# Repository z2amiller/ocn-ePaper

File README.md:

# ocn-ePaper

A battery-powered elapsed-time counter with a 2.13-inch e-paper display and a magnetic off switch.
While a magnet sits at the marked end, the board is switched off. Take the magnet away and it powers
up and counts elapsed time in hours and minutes, up to 99:59 (about 100 hours). Put the magnet back
and it powers down several seconds later, leaving the last count on the display; the next time the
magnet comes off, counting starts again from 00:00.

It is the e-paper version of [ocn-LCD](https://github.com/z2amiller/ocn-LCD), which uses a segment
LCD.

The renders leave out the e-paper panel (it lies over the front), its socket, the reed switch and the
CR123A holder (on the back), which have no 3D models. They show a header in J1, which stays empty on
a finished board.

Status: revision 0.1, not yet built. Firmware will be added to this repository. The folded tail's pin
order has not yet been checked against a real panel.

## How it works

- **Counting.** An MSP430FR2111 keeps time from a 32.768 kHz crystal. It spends almost all its time
  in its deepest sleep mode with only the clock running, and wakes to update the display.
- **Display.** The panel is a Good Display GDEY0213B74: 2.13 inches, 250 × 122 pixels, black and
  white. E-paper holds its image with no power at all, so the panel sleeps between updates, and the
  last count stays on the screen after the board powers down. Updating it takes higher positive and
  negative voltages. The panel's own controller makes them with a small boost converter on the board
  (L1, Q2, D1–D3), which runs only during an update.
- **Mounting.** The panel lies display-up over the front of the board, 3 mm above it, with its tail
  folded under it into a socket (DS2) on the board. Every part on the front fits under it; the
  tallest, L1, is 2.6 mm.
- **Power.** A CR123A lithium cell (3 V, about 1,500 mAh) in a holder on the back.
- **Magnet switch.** The magnet closes a normally open reed switch (SW1). That pulls the gate of a
  P-channel MOSFET (Q1) up to the cell voltage and cuts power to everything after it. With the
  magnet away, a 10 MΩ resistor pulls the gate low and the board runs. While switched off, the only
  drain on the cell is that resistor, about 0.3 µA.
- **Reset on purpose, not by accident.** About 20 µF of capacitance after the switch keeps the board
  running for several seconds after the magnet arrives (roughly 5–15 s, depending on the panel's
  sleep current), so a brief knock or switch bounce does not reset the count. Leaving the magnet in
  place longer than that powers the board down. If the magnet arrives during a display update, which
  draws about 3.5 mA, the board stops within milliseconds and the image may be left half-updated
  until the next power-up.

## Power budget

Estimates at 3.0 V and 25 °C, from the TI datasheet (SLASE78) and Good Display's spec for the panel.
They will be replaced by measurements once the firmware is in.

| Item | Counting (magnet away) | Off (magnet in place) | Basis |
|---|---|---|---|
| MCU asleep (LPM3.5), with the 32 kHz crystal and RTC running | 0.44 µA | 0 | Datasheet 0.66 µA typical with the supervisor (SVS) on; turning it off saves about 0.22 µA |
| Panel controller in deep sleep between updates | 1 µA (5 µA max) | 0 | Good Display spec |
| Display updates, once a minute | ~50 µA | 0 | 3.5 mA while updating, 0.42 s for a partial update and 3 s for a full one, with a full refresh after every five partial ones as Good Display recommends |
| MCU awake for each update (writing the image, waiting on BUSY) | ~0.2 µA | 0 | ~10 ms at ~1 mA per update, then light sleep while the panel updates |
| Gate pull-down R3 (10 MΩ across the cell while the reed is closed) | 0 | 0.3 µA | 3.0 V / 10 MΩ |
| Q1 MOSFET leakage while off | – | a few nA | Typical; the datasheet maximum is specified at 30 V |
| Hold-up capacitors, leakage | ~1 nA | 0 | MLCC insulation resistance |
| Reset pull-up, reed switch, unused pins (driven low) | 0 | 0 | No DC path |
| **Total** | **about 52 µA** | **about 0.3 µA** | |

The display updates dominate. One partial update uses as much charge as about 17 minutes of sleep,
and a full refresh as about 2 hours, so the update rate sets the battery life.

Estimated runtime on one CR123A (1,500 mAh nominal), allowing about 1 %/year for the cell's own
self-discharge:

| Mode | Average draw | Estimated runtime |
|---|---|---|
| Counting, display updated once a minute | about 52 µA | about 3 years |
| Counting, display updated every 10 minutes | about 6–10 µA | over 10 years |
| Off (magnet in place) | about 0.3 µA | decades |

The last two are longer than a CR123A's rated shelf life of about 10 years, so in practice the cell's
age sets the limit, not this circuit. Cold reduces the cell's usable capacity, and the panel is
specified to update only between 0 and 50 °C.

Firmware choices that keep it there:
- Update the count once a minute at most; slower updates last much longer.
- Use partial updates, with a full refresh after every five to keep ghosting down.
- Put the panel in deep sleep after each update, and sleep in LPM3 while BUSY is high. Check BUSY
  again after its falling edge wakes the MCU, before sending the next command.
- Leave the voltage supervisor (SVS) off in LPM3.5; it costs about 0.2 µA. The brownout reset stays
  on regardless.
- Keep the panel's RES line driven while the panel is in use, and drive every unused pin low.

## Placing the magnet

The reed switch is at the end marked MAGNET DISABLE and runs along the length of the board. It
responds to field along its own length, so use a magnet magnetized through its flat faces (a
neodymium cylinder or disc), at that end, with its axis along the board and its face toward the
board's end. SW1's axis is 3.2 mm from the board's centreline, so a magnet centred on the board's end
lines up with it closely. A model of a typical 10 × 8 mm N42 cylinder (no nearby steel) gives several
times the switch's ~2–3 mT pull-in out to about 20 mm, even 9 mm off the switch's axis.

**Steel nearby.** The CR123A's case is steel, and it sits on the back directly behind the switch.
That changes the field around the switch, and its effect hasn't been measured yet. Check the
switching distance on the bench with a cell fitted.

The switch lets go only once the magnet is a few centimeters away (the same model puts it at about
35–40 mm in line), so move the magnet well clear to start counting.

## Key parts

| Ref | Part | LCSC |
|---|---|---|
| U1 | TI MSP430FR2111IPW, TSSOP-16 | C2052845 |
| DS2 | Good Display GDEY0213B74 2.13" e-paper panel, in a Hirose FH34SRJ-24S-0.5SH socket | C324726 (the socket) |
| BT1 | MYOUNG BH-123A-A1CJ002 CR123A holder, through-hole | C5290177 |
| SW1 | Littelfuse 59170-1-S-00-D reed switch, normally open, 10–15 AT | C315909 |
| Q1 | AO3401A P-channel MOSFET, SOT-23 (power switch) | C15127 |
| Q2 | Vishay Si1308EDL N-channel MOSFET, SOT-323 (display booster) | C469327 |
| L1 | Changjiang FNR4030S470MT 47 µH inductor, 4 × 4 mm | C167888 |
| D1–D3 | 1N5819WS Schottky diode, SOD-323 | C191023 |
| Y1 | 32.768 kHz crystal, 3215, 12.5 pF | C32346 |

Every part in the BOM carries its LCSC number. The panel itself comes from Good Display; DS2's BOM
line is its socket. J1 and TP3 are left out of the BOM and the placement file, and so are BT1 and
SW1, which are fitted by hand. The passives are 0603 and 1206.

## Assembly

1. **Surface-mount parts, all on the front.** A stencil helps with the 0.65 mm pitch MCU. The reed
   switch is rated for reflow and can go on with the rest.
2. **CR123A holder on the back, by hand.** Trim its two pins close on the front afterwards. Untrimmed,
   they stand about 2.5 mm proud, under a panel that sits 3 mm up.
3. **Program the MCU** (see below). J1 ends up under the panel, so do this before the panel goes on.
4. **Panel.** Open the socket's latch and slide the tail in, with the panel lying face down beyond the
   end of the board nearest the socket, then close the latch. Fold the panel over onto a 3 mm spacer on the front, so it lies
   display-up over the board. Double-sided foam tape works as the spacer and keeps pressure off the
   glass.
5. **Battery.** Fit the CR123A last, matching the + and − marks on the back.

## Programming

The MCU is programmed over Spy-Bi-Wire from the eZ-FET programmer on a TI MSP-EXP430FR4133
LaunchPad. Any MSP430 LaunchPad with an eZ-FET should also work. J1, on the board's long edge,
carries the four programming signals plus the MCU's serial port. It is a row of six 0.1-inch holes
that stays empty: the panel covers it once fitted.

1. **Take the cell out.** The LaunchPad powers the board at 3.3 V. With the magnet away, Q1 is on
   and would pass that straight back into the cell, and a CR123A must never be charged. The
   silkscreen beside J1 says so too.
2. **Pull every jumper off the LaunchPad's J101 isolation block.** That disconnects the
   LaunchPad's own MCU, so the eZ-FET talks only to this board.
3. **Connect J1.** Push a straight 6-pin header into J1's holes without soldering it, holding it
   tilted slightly so the pins press against the hole walls. Wire it to J101 with dupont jumpers,
   using the J101 pins on the eZ-FET (emulator) side, not the side that runs to the LaunchPad's own
   MCU:

   | ocn-ePaper J1 | LaunchPad J101, eZ-FET side |
   |---|---|
   | 3V | 3V3 |
   | R | SBW RST |
   | T | SBW TST |
   | GND | GND |
   | RX (optional, serial) | RXD |
   | TX (optional, serial) | TXD |

   The serial names match straight across. J101 labels its pins from the target MCU's point of
   view, so its RXD carries data into this board's RX.

4. **Flash the firmware** with TI UniFlash or Code Composer Studio. Select the MSP430FR2111 and the
   LaunchPad's eZ-FET as the connection. A command-line recipe will come with the firmware.
5. **Unplug the LaunchPad before measuring current or fitting the cell.** The programming and
   serial lines draw current of their own.

**Serial port.** RX and TX are on P1.2 and P1.3. They share the MCU's only serial block with the
panel's SPI, so firmware switches the block between the two.

**Measuring battery current.** R2 (1 Ω, 1206) sits in series with the cell. Lift it and connect a
current meter across its pads. TP3 is a test pad on the switched 3 V supply.

## Files

- `ocn-ePaper.kicad_pro`, `.kicad_sch` and `.kicad_pcb`: the KiCad 10 project. The board is
  27 × 65.3 mm, two layers.
- `lib/`: the board's own symbols and footprints: the MSP430FR2111, the GDEY0213B74 and its
  folded-tail footprint (the socket, plus the panel's outline on the User.Drawings layer), the CR123A
  holder and the reed switch. The project's library tables point at this folder, so the project opens
  without any other library installed.

## License

Licensed under the **CERN Open Hardware Licence Version 2 – Permissive**
(CERN-OHL-P v2). See [LICENSE](LICENSE) and [NOTICE](NOTICE).

You may make, modify, and sell boards from these files, with no obligation to
publish your changes.

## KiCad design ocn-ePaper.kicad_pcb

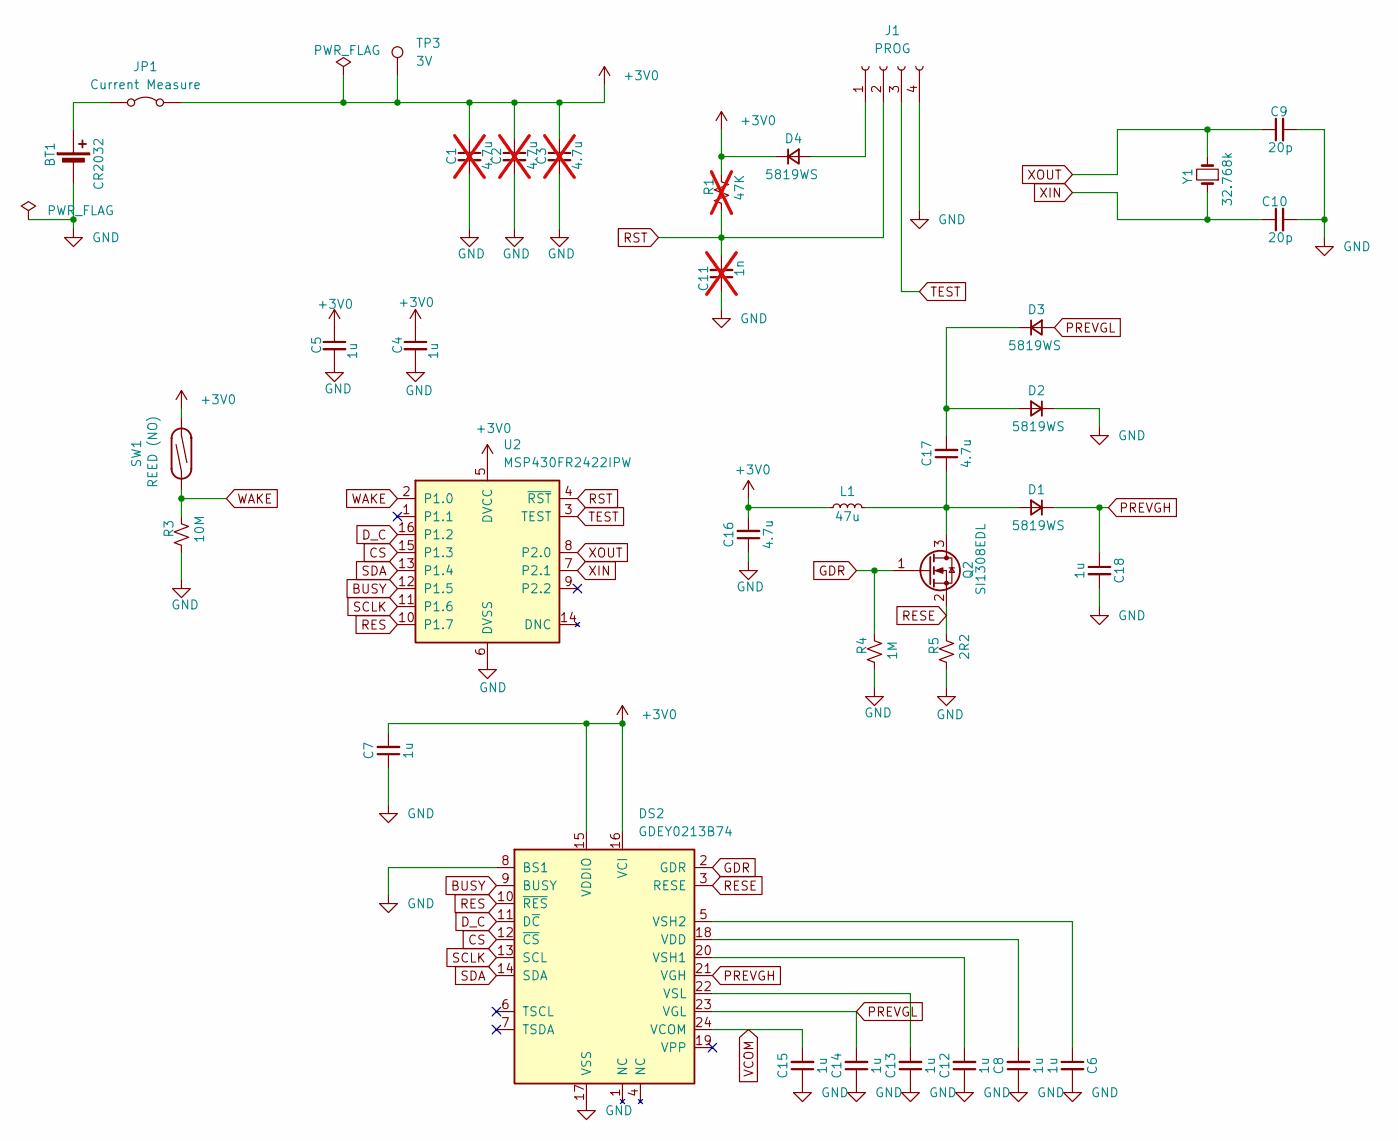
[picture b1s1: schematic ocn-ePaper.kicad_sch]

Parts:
BT1: CR2032; BatteryHolder_LianXin_BS-CR2032-8_1x2032; LCSC C7498149
C1, C2, C3: 4.7u; C_1206_3216Metric; LCSC C29823; not fitted
C4, C5, C6, C7, C8, C12, C13, C14, C15, C18: 1u; C_0603_1608Metric; LCSC C15849
C9, C10: 20p; C_0603_1608Metric; LCSC C1648
C11: 1n; C_0603_1608Metric; LCSC C1588; not fitted
C16, C17: 4.7u; C_1206_3216Metric; LCSC C29823
D1, D2, D3, D4: 5819WS; D_SOD-323F; LCSC C191023
DS2: GDEY0213B74; EPD_GDEY0213B74_WrappedToBack_Hirose_FH34SRJ-24S-0.5SH; LCSC C324726
J1: PROG; PinHeader_1x04_P2.54mm_Vertical
JP1: Current Measure; SolderJumper-2_P1.3mm_Bridged_Pad1.0x1.5mm
L1: 47u; L_Changjiang_FNR4030S; LCSC C167888
Q2: SI1308EDL; SOT-323_SC-70; LCSC C469327
R1: 47K; R_0603_1608Metric; LCSC C25819; not fitted
R3: 10M; R_0603_1608Metric; LCSC C7250
R4: 1M; R_0603_1608Metric; LCSC C22935
R5: 2R2; R_0603_1608Metric; LCSC C22939
SW1: REED (NO); SW_SPST_REED_Littelfuse_59170_GullWing; LCSC C315909
TP3: 3V; TestPoint_Pad_1.5x1.5mm
U2: MSP430FR2422IPW; TSSOP-16_4.4x5mm_P0.65mm; LCSC C191019
Y1: 32.768k; Crystal_SMD_3215-2Pin_3.2x1.5mm; LCSC C271654

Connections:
+3V0: C1.1, C2.1, C3.1, C4.1, C5.1, C7.2, C16.2, D4.1 (K), DS2.15 (VDDIO), DS2.16 (VCI), JP1.2 (B), L1.1, R1.1, SW1.2, TP3.1 (1_1), U2.5 (DVCC)
BUSY: DS2.9 (BUSY), U2.12 (P1.5)
CS: DS2.12 (~CS), U2.15 (P1.3)
D_C: DS2.11 (D~C), U2.16 (P1.2)
GDR: DS2.2 (GDR), Q2.1 (G), R4.1
GND: BT1.2 (-), C1.2, C2.2, C3.2, C4.2, C5.2, C6.2, C7.1, C8.1, C9.2, C10.2, C11.1, C12.1, C13.1, C14.1, C15.1, C16.1, C18.2, D2.1 (K), DS2.8 (BS1), DS2.17 (VSS), J1.4, R3.2, R4.2, R5.2, U2.6 (DVSS)
unnamed: BT1.1 (+), JP1.1 (A)
unnamed: C17.1, D1.2 (A), L1.2, Q2.3 (D)
unnamed: C17.2, D2.2 (A), D3.1 (K)
unnamed: D4.2 (A), J1.1
unnamed: C8.2, DS2.18 (VDD)
unnamed: C12.2, DS2.20 (VSH1)
unnamed: C6.1, DS2.5 (VSH2)
unnamed: C13.2, DS2.22 (VSL)
PREVGH: C18.1, D1.1 (K), DS2.21 (VGH)
PREVGL: C14.2, D3.2 (A), DS2.23 (VGL)
RES: DS2.10 (~RES), U2.10 (P1.7)
RESE: DS2.3 (RESE), Q2.2 (S), R5.1
RST: C11.2, J1.2, R1.2, U2.4 (~RST)
SCLK: DS2.13 (SCL), U2.11 (P1.6)
SDA: DS2.14 (SDA), U2.13 (P1.4)
TEST: J1.3, U2.3 (TEST)
VCOM: C15.2, DS2.24 (VCOM)
WAKE: R3.1, SW1.1, U2.2 (P1.0)
XIN: C10.1, U2.7 (P2.1), Y1.1
XOUT: C9.1, U2.8 (P2.0), Y1.2

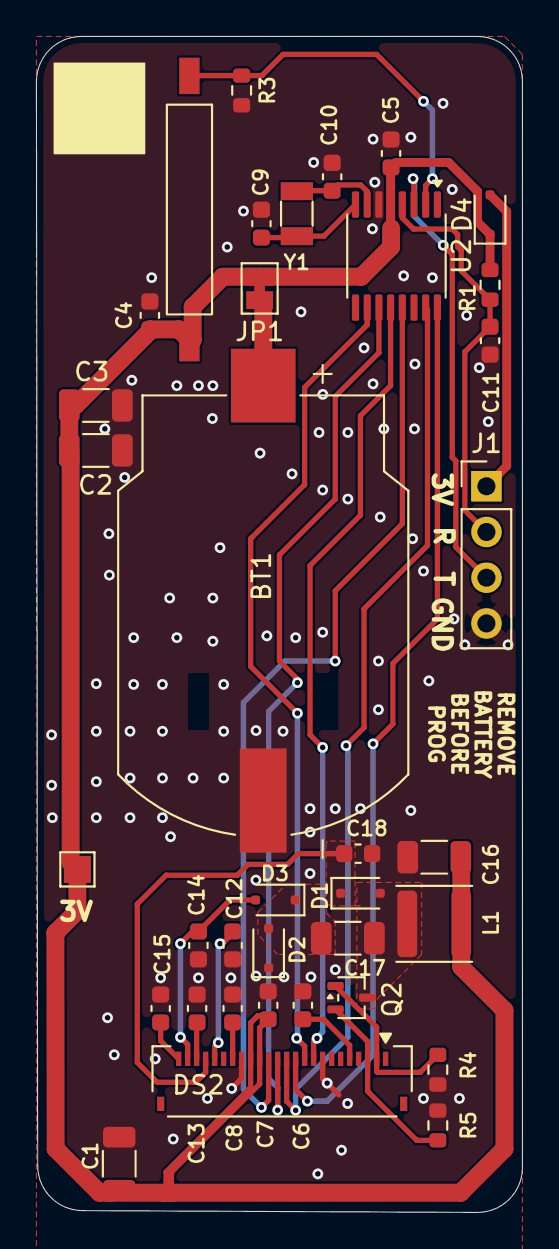
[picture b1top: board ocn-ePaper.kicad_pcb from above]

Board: 2 copper layers, 27.0 x 65.3 mm, 36 parts (0 on the bottom side), 26 nets.
